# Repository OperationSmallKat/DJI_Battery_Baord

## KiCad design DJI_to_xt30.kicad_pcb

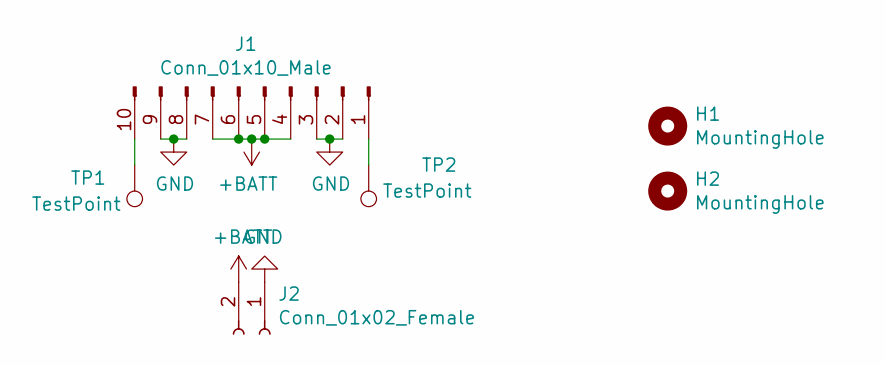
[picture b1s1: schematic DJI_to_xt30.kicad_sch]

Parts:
H1, H2: MountingHole; MountingHole_3.2mm_M3
J1: Conn_01x10_Male; JST_EH_B10B-EH-A_1x10_P2.50mm_Vertical
J2: Conn_01x02_Female; XT-30_female
TP1, TP2: TestPoint; TestPoint_Pad_1.5x1.5mm

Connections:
+BATT: J1.4, J1.5, J1.6, J1.7, J2.2
GND: J1.2, J1.3, J1.8, J1.9, J2.1
unnamed: J1.1, TP2.1
unnamed: J1.10, TP1.1

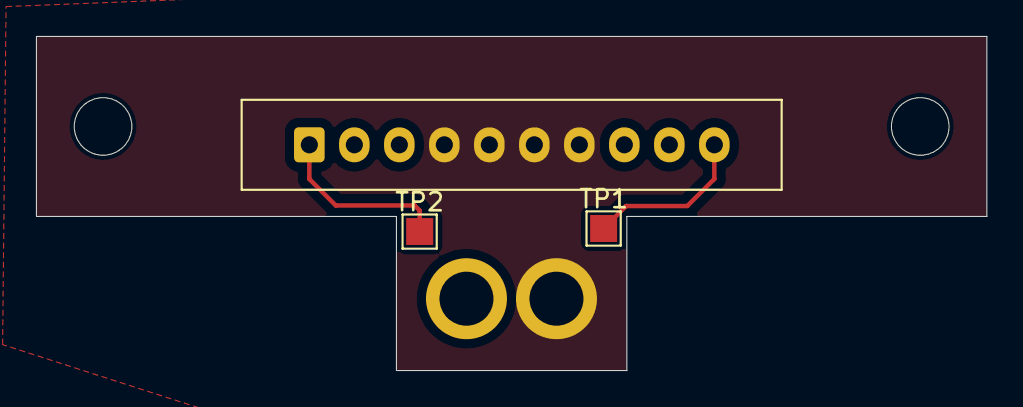
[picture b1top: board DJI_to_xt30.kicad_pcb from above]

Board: 2 copper layers, 52.8 x 18.6 mm, 6 parts (1 on the bottom side), 4 nets.

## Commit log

2024-02-03 Updated to kicad 7, Added image.
